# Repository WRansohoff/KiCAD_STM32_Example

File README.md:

# Overview

This is just an example KiCAD project for an STM32F031K6 breakout board.

I hope it's about what someone would wind up with after following this tutorial:

https://vivonomicon.com/2018/05/05/your-own-hardware-designing-an-stm32-development-board/

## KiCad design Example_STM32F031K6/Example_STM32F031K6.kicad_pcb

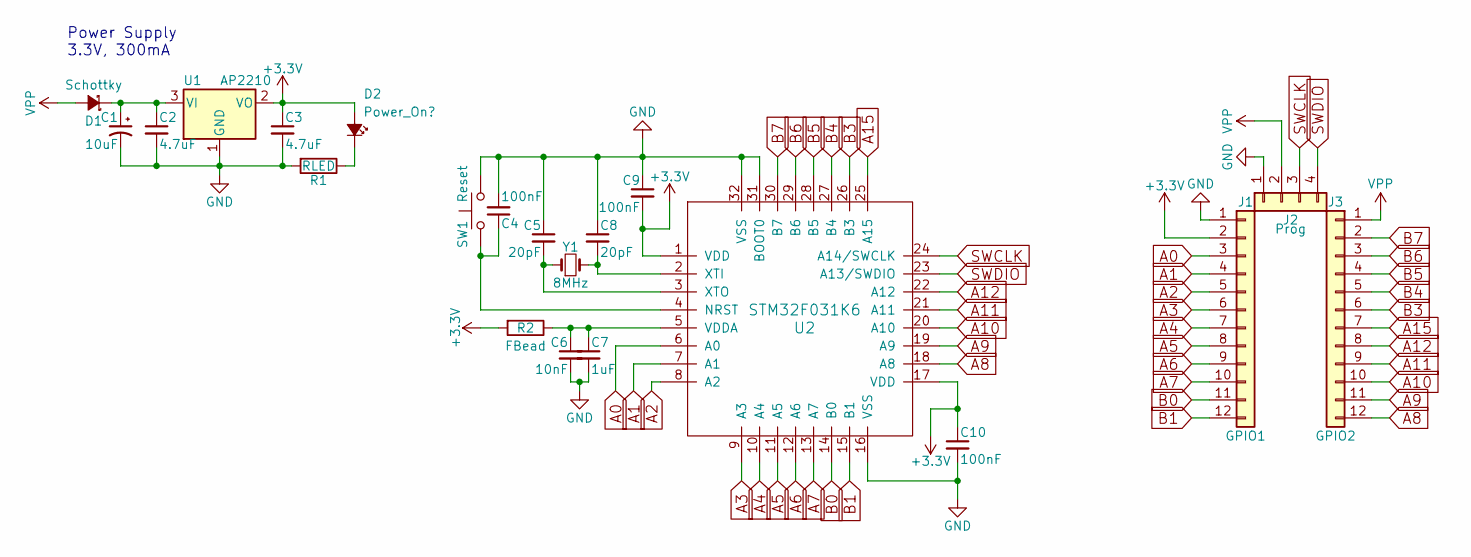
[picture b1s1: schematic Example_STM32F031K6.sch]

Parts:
C1: 10uF; CP_Tantalum_Case-A_EIA-3216-18_Hand
C2, C3: 4.7uF; C_0805_HandSoldering
C4, C9, C10: 100nF; C_0805_HandSoldering
C5, C8: 20pF; C_0805_HandSoldering
C6: 10nF; C_0805_HandSoldering
C7: 1uF; C_0805_HandSoldering
D1: Schottky; D_SOD-123
D2: Power_On?; LED_0805_HandSoldering
J1: GPIO1; Pin_Header_Straight_1x12_Pitch2.54mm
J2: Prog; Pin_Header_Angled_1x04_Pitch2.54mm
J3: GPIO2; Pin_Header_Straight_1x12_Pitch2.54mm
R1: RLED; R_0805_HandSoldering
R2: FBead; R_0805_HandSoldering
SW1: Reset; SW_PUSH_6mm
U1: AP2210; SOT-23_Handsoldering
U2: STM32F031K6; LQFP-32_7x7mm_Pitch0.8mm
Y1: 8MHz; Crystal_Round_d3.0mm_Vertical

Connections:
+3V3: C3.1, C9.2, C10.1, D2.2 (A), J1.2, R2.2, U1.2 (VO), U2.1 (VDD), U2.17 (VDD)
A0: J1.3, U2.6 (A0)
A1: J1.4, U2.7 (A1)
A2: J1.5, U2.8 (A2)
A3: J1.6, U2.9 (A3)
A4: J1.7, U2.10 (A4)
A5: J1.8, U2.11 (A5)
A6: J1.9, U2.12 (A6)
A7: J1.10, U2.13 (A7)
A8: J3.12, U2.18 (A8)
A9: J3.11, U2.19 (A9)
A10: J3.10, U2.20 (A10)
A11: J3.9, U2.21 (A11)
A12: J3.8, U2.22 (A12)
A15: J3.7, U2.25 (A15)
B0: J1.11, U2.14 (B0)
B1: J1.12, U2.15 (B1)
B3: J3.6, U2.26 (B3)
B4: J3.5, U2.27 (B4)
B5: J3.4, U2.28 (B5)
B6: J3.3, U2.29 (B6)
B7: J3.2, U2.30 (B7)
GND: C1.2, C2.2, C3.2, C4.2, C5.1, C6.2, C7.2, C8.1, C9.1, C10.2, J1.1, J2.1, R1.2, SW1.1, U1.1 (GND), U2.16 (VSS), U2.31 (BOOT0), U2.32 (VSS)
unnamed: C1.1, C2.1, D1.1 (K), U1.3 (VI)
unnamed: C4.1, SW1.2, U2.4 (NRST)
unnamed: C5.2, U2.3 (XTO), Y1.1
unnamed: C6.1, C7.1, R2.1, U2.5 (VDDA)
unnamed: C8.2, U2.2 (XTI), Y1.2
unnamed: D2.1 (K), R1.1
SWCLK: J2.3, U2.24 (A14/SWCLK)
SWDIO: J2.4, U2.23 (A13/SWDIO)
VPP: D1.2 (A), J2.2, J3.1

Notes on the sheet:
Power Supply 3.3V, 300mA

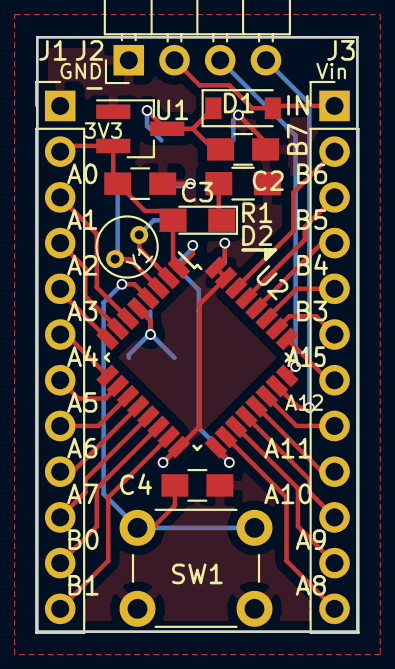
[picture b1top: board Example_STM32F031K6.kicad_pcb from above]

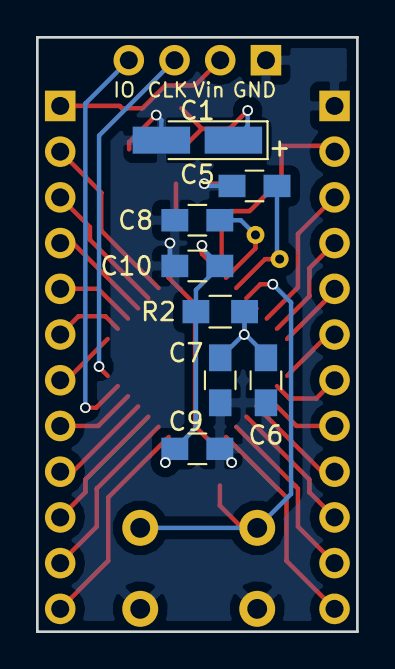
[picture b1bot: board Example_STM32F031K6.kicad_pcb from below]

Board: 2 copper layers, 17.8 x 33.0 mm, 21 parts (8 on the bottom side), 32 nets.

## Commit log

2018-05-05 Initial commit; this includes the project and library, but I worry that KiCAD might use some non-local paths...
2018-05-05 Add a readme
